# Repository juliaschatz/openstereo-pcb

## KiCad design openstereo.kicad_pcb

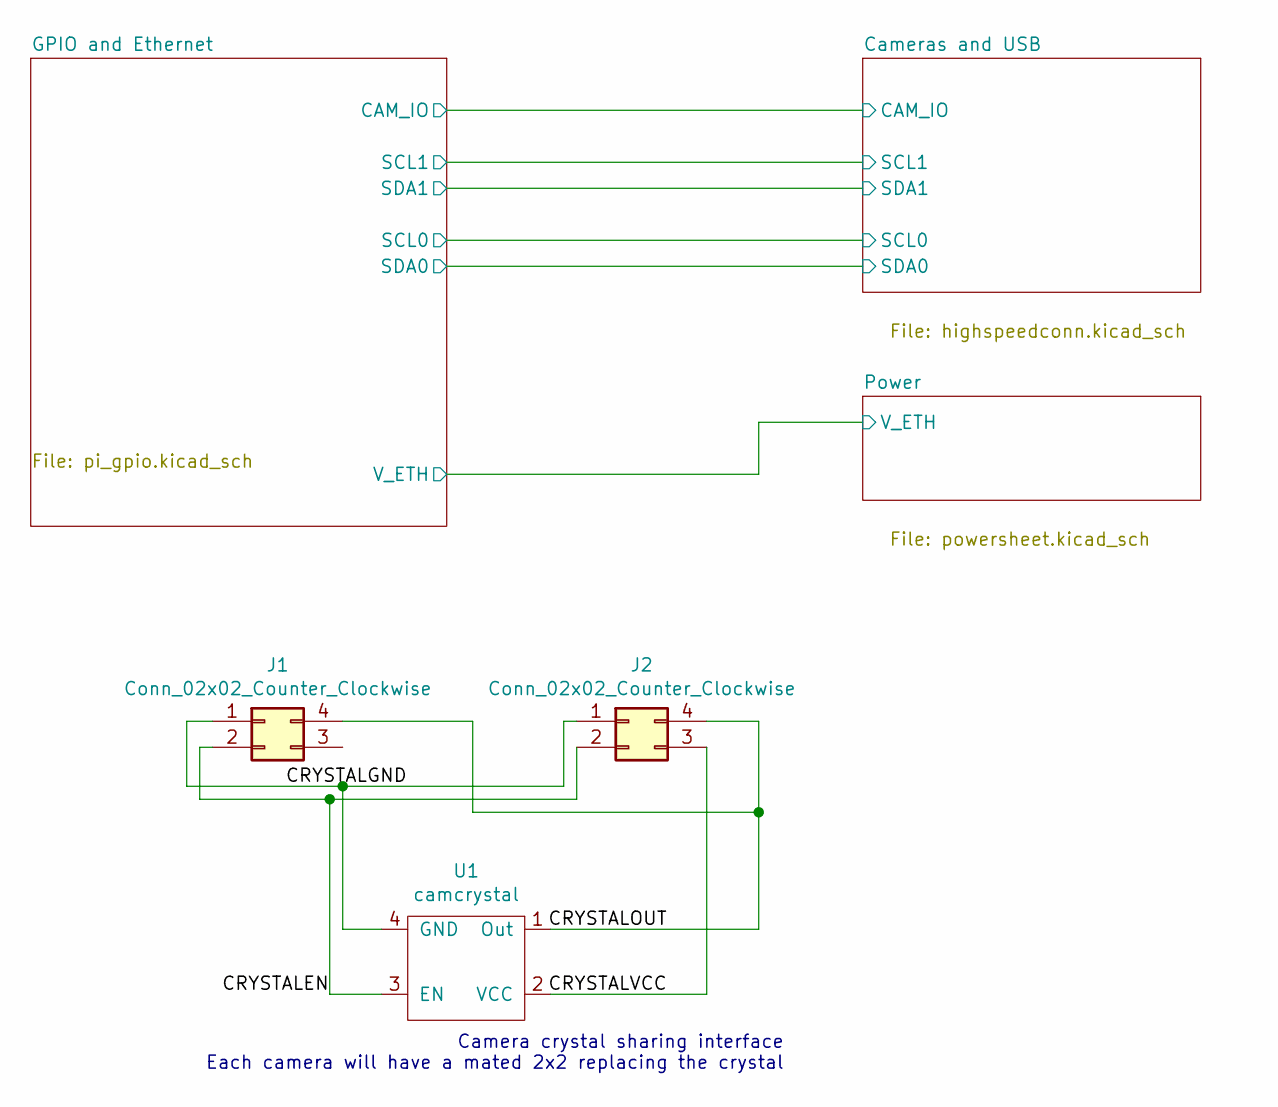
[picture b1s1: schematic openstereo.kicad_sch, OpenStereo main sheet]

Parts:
J1, J2: Conn_02x02_Counter_Clockwise; PinHeader_2x02_P1.27mm_Vertical
U1: camcrystal; crystalpad

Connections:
/CRYSTALEN: J1.2, J2.2, U1.3 (EN)
/CRYSTALGND: J1.1, J2.1, U1.4 (GND)
/CRYSTALOUT: J1.4, J2.4, U1.1 (Out)
/CRYSTALVCC: J2.3, U1.2 (VCC)

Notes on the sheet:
Camera crystal sharing interface Each camera will have a mated 2x2 replacing the crystal

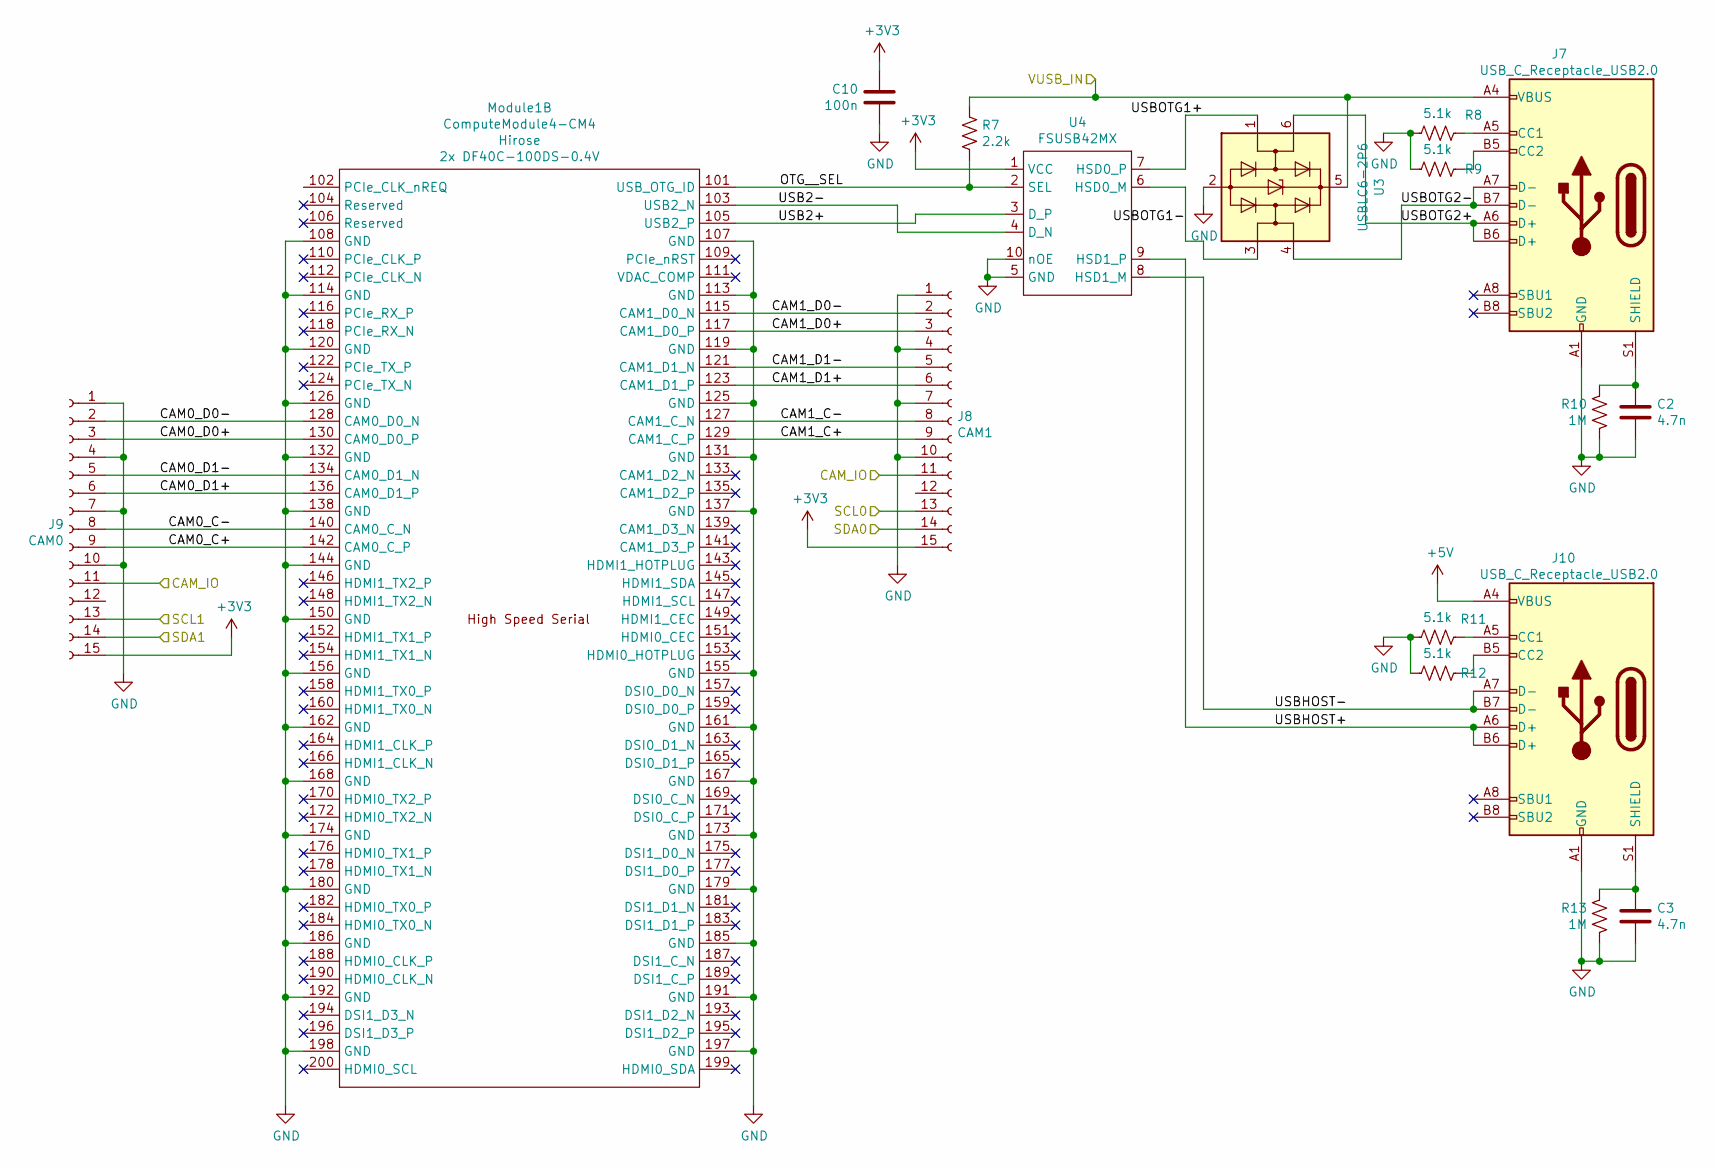
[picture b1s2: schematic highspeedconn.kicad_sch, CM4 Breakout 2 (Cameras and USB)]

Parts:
C2, C3: 4.7n; C_0603_1608Metric
C10: 100n; C_0603_1608Metric
J7, J10: USB_C_Receptacle_USB2.0; USB_C_Receptacle_HRO_TYPE-C-31-M-12
J8: CAM1; SFW15R-2STE1LF
J9: CAM0; SFW15R-2STE1LF
Module1: ComputeModule4-CM4; Raspberry-Pi-4-Compute-Module
R7: 2.2k; R_0603_1608Metric
R8, R9, R11, R12: 5.1k; R_0603_1608Metric
R10, R13: 1M; R_0603_1608Metric
U3: USBLC6-2P6; SOT-666
U4: FSUSB42MX; 10-MSOP-FSUSB

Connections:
+3V3: C10.2, J8.15, J9.15, U4.1 (VCC); also elsewhere on the board
+5V: J10.A4 (VBUS), J10.A9 (VBUS), J10.B4 (VBUS), J10.B9 (VBUS); also elsewhere on the board
/CAM_IO: J8.11, J9.11; also elsewhere on the board
/Cameras and USB/CAM0_C+: J9.9, Module1.142 (CAM0_C_P)
/Cameras and USB/CAM0_C-: J9.8, Module1.140 (CAM0_C_N)
/Cameras and USB/CAM0_D0+: J9.3, Module1.130 (CAM0_D0_P)
/Cameras and USB/CAM0_D0-: J9.2, Module1.128 (CAM0_D0_N)
/Cameras and USB/CAM0_D1+: J9.6, Module1.136 (CAM0_D1_P)
/Cameras and USB/CAM0_D1-: J9.5, Module1.134 (CAM0_D1_N)
/Cameras and USB/CAM1_C+: J8.9, Module1.129 (CAM1_C_P)
/Cameras and USB/CAM1_C-: J8.8, Module1.127 (CAM1_C_N)
/Cameras and USB/CAM1_D0+: J8.3, Module1.117 (CAM1_D0_P)
/Cameras and USB/CAM1_D0-: J8.2, Module1.115 (CAM1_D0_N)
/Cameras and USB/CAM1_D1+: J8.6, Module1.123 (CAM1_D1_P)
/Cameras and USB/CAM1_D1-: J8.5, Module1.121 (CAM1_D1_N)
/Cameras and USB/OTG__SEL: Module1.101 (USB_OTG_ID), R7.2, U4.2 (SEL)
/Cameras and USB/USB2+: Module1.105 (USB2_P), U4.3 (D_P)
/Cameras and USB/USB2-: Module1.103 (USB2_N), U4.4 (D_N)
/Cameras and USB/USBHOST+: J10.A6 (D+), J10.B6 (D+), U4.9 (HSD1_P)
/Cameras and USB/USBHOST-: J10.A7 (D-), J10.B7 (D-), U4.8 (HSD1_M)
/Cameras and USB/USBOTG1+: U3.1 (I/O1), U4.7 (HSD0_P)
/Cameras and USB/USBOTG1-: U3.3 (I/O2), U4.6 (HSD0_M)
/Cameras and USB/USBOTG2+: J7.A6 (D+), J7.B6 (D+), U3.6 (I/O1)
/Cameras and USB/USBOTG2-: J7.A7 (D-), J7.B7 (D-), U3.4 (I/O2)
/Cameras and USB/VUSB_IN: J7.A4 (VBUS), J7.A9 (VBUS), J7.B4 (VBUS), J7.B9 (VBUS), R7.1, U3.5 (VBUS)
/SCL0: J8.13; also elsewhere on the board
/SCL1: J9.13; also elsewhere on the board
/SDA0: J8.14; also elsewhere on the board
/SDA1: J9.14; also elsewhere on the board
GND: C2.1, C3.1, C10.1, J7.A1 (GND), J7.A12 (GND), J7.B1 (GND), J7.B12 (GND), J8.1, J8.4, J8.7, J8.10, J9.1, J9.4, J9.7, J9.10, J10.A1 (GND), J10.A12 (GND), J10.B1 (GND), J10.B12 (GND), Module1.107 (GND), Module1.108 (GND), Module1.113 (GND), Module1.114 (GND), Module1.119 (GND), Module1.120 (GND), Module1.125 (GND), Module1.126 (GND), Module1.131 (GND), Module1.132 (GND), Module1.137 (GND), Module1.138 (GND), Module1.144 (GND), Module1.150 (GND), Module1.155 (GND), Module1.156 (GND), Module1.161 (GND), Module1.162 (GND), Module1.167 (GND), Module1.168 (GND), Module1.173 (GND), Module1.174 (GND), Module1.179 (GND), Module1.180 (GND), Module1.185 (GND), Module1.186 (GND), Module1.191 (GND), Module1.192 (GND), Module1.197 (GND), Module1.198 (GND), R8.1, R9.1, R10.1, R11.1, R12.1, R13.1, U3.2 (GND), U4.5 (GND), U4.10 (nOE); also elsewhere on the board
unnamed: C2.2, J7.S1 (SHIELD), R10.2
unnamed: C3.2, J10.S1 (SHIELD), R13.2
unnamed: J7.A5 (CC1), R8.2
unnamed: J7.B5 (CC2), R9.2
unnamed: J10.A5 (CC1), R11.2
unnamed: J10.B5 (CC2), R12.2
no_connect_106: J10.A8 (SBU1)
no_connect_107: J10.B8 (SBU2)
no_connect_110: J7.A8 (SBU1)
no_connect_111: J7.B8 (SBU2)
no_connect_113: Module1.104 (Reserved)
no_connect_114: Module1.106 (Reserved)
no_connect_115: Module1.109 (PCIe_nRST)
no_connect_116: Module1.110 (PCIe_CLK_P)
no_connect_117: Module1.111 (VDAC_COMP)
no_connect_118: Module1.112 (PCIe_CLK_N)
no_connect_119: Module1.116 (PCIe_RX_P)
no_connect_120: Module1.118 (PCIe_RX_N)
no_connect_121: Module1.122 (PCIe_TX_P)
no_connect_122: Module1.124 (PCIe_TX_N)
no_connect_123: Module1.133 (CAM1_D2_N)
no_connect_124: Module1.135 (CAM1_D2_P)
no_connect_125: Module1.139 (CAM1_D3_N)
no_connect_126: Module1.141 (CAM1_D3_P)
no_connect_127: Module1.143 (HDMI1_HOTPLUG)
no_connect_128: Module1.145 (HDMI1_SDA)
no_connect_129: Module1.146 (HDMI1_TX2_P)
no_connect_130: Module1.147 (HDMI1_SCL)
no_connect_131: Module1.148 (HDMI1_TX2_N)
no_connect_132: Module1.149 (HDMI1_CEC)
no_connect_133: Module1.151 (HDMI0_CEC)
no_connect_134: Module1.152 (HDMI1_TX1_P)
no_connect_135: Module1.153 (HDMI0_HOTPLUG)
no_connect_136: Module1.154 (HDMI1_TX1_N)
no_connect_137: Module1.157 (DSI0_D0_N)
no_connect_138: Module1.158 (HDMI1_TX0_P)
no_connect_139: Module1.159 (DSI0_D0_P)
no_connect_141: Module1.160 (HDMI1_TX0_N)
no_connect_142: Module1.163 (DSI0_D1_N)
no_connect_143: Module1.164 (HDMI1_CLK_P)
no_connect_144: Module1.165 (DSI0_D1_P)
no_connect_145: Module1.166 (HDMI1_CLK_N)
no_connect_146: Module1.169 (DSI0_C_N)
no_connect_147: Module1.170 (HDMI0_TX2_P)
no_connect_148: Module1.171 (DSI0_C_P)
no_connect_149: Module1.172 (HDMI0_TX2_N)
no_connect_150: Module1.175 (DSI1_D0_N)
no_connect_151: Module1.176 (HDMI0_TX1_P)
no_connect_152: Module1.177 (DSI1_D0_P)
no_connect_153: Module1.178 (HDMI0_TX1_N)
no_connect_155: Module1.181 (DSI1_D1_N)
no_connect_156: Module1.182 (HDMI0_TX0_P)
no_connect_157: Module1.183 (DSI1_D1_P)
no_connect_158: Module1.184 (HDMI0_TX0_N)
no_connect_159: Module1.187 (DSI1_C_N)
no_connect_160: Module1.188 (HDMI0_CLK_P)
no_connect_161: Module1.189 (DSI1_C_P)
no_connect_163: Module1.190 (HDMI0_CLK_N)
no_connect_164: Module1.193 (DSI1_D2_N)
no_connect_165: Module1.194 (DSI1_D3_N)
no_connect_166: Module1.195 (DSI1_D2_P)
no_connect_167: Module1.196 (DSI1_D3_P)
no_connect_168: Module1.199 (HDMI0_SDA)
no_connect_169: Module1.200 (HDMI0_SCL)

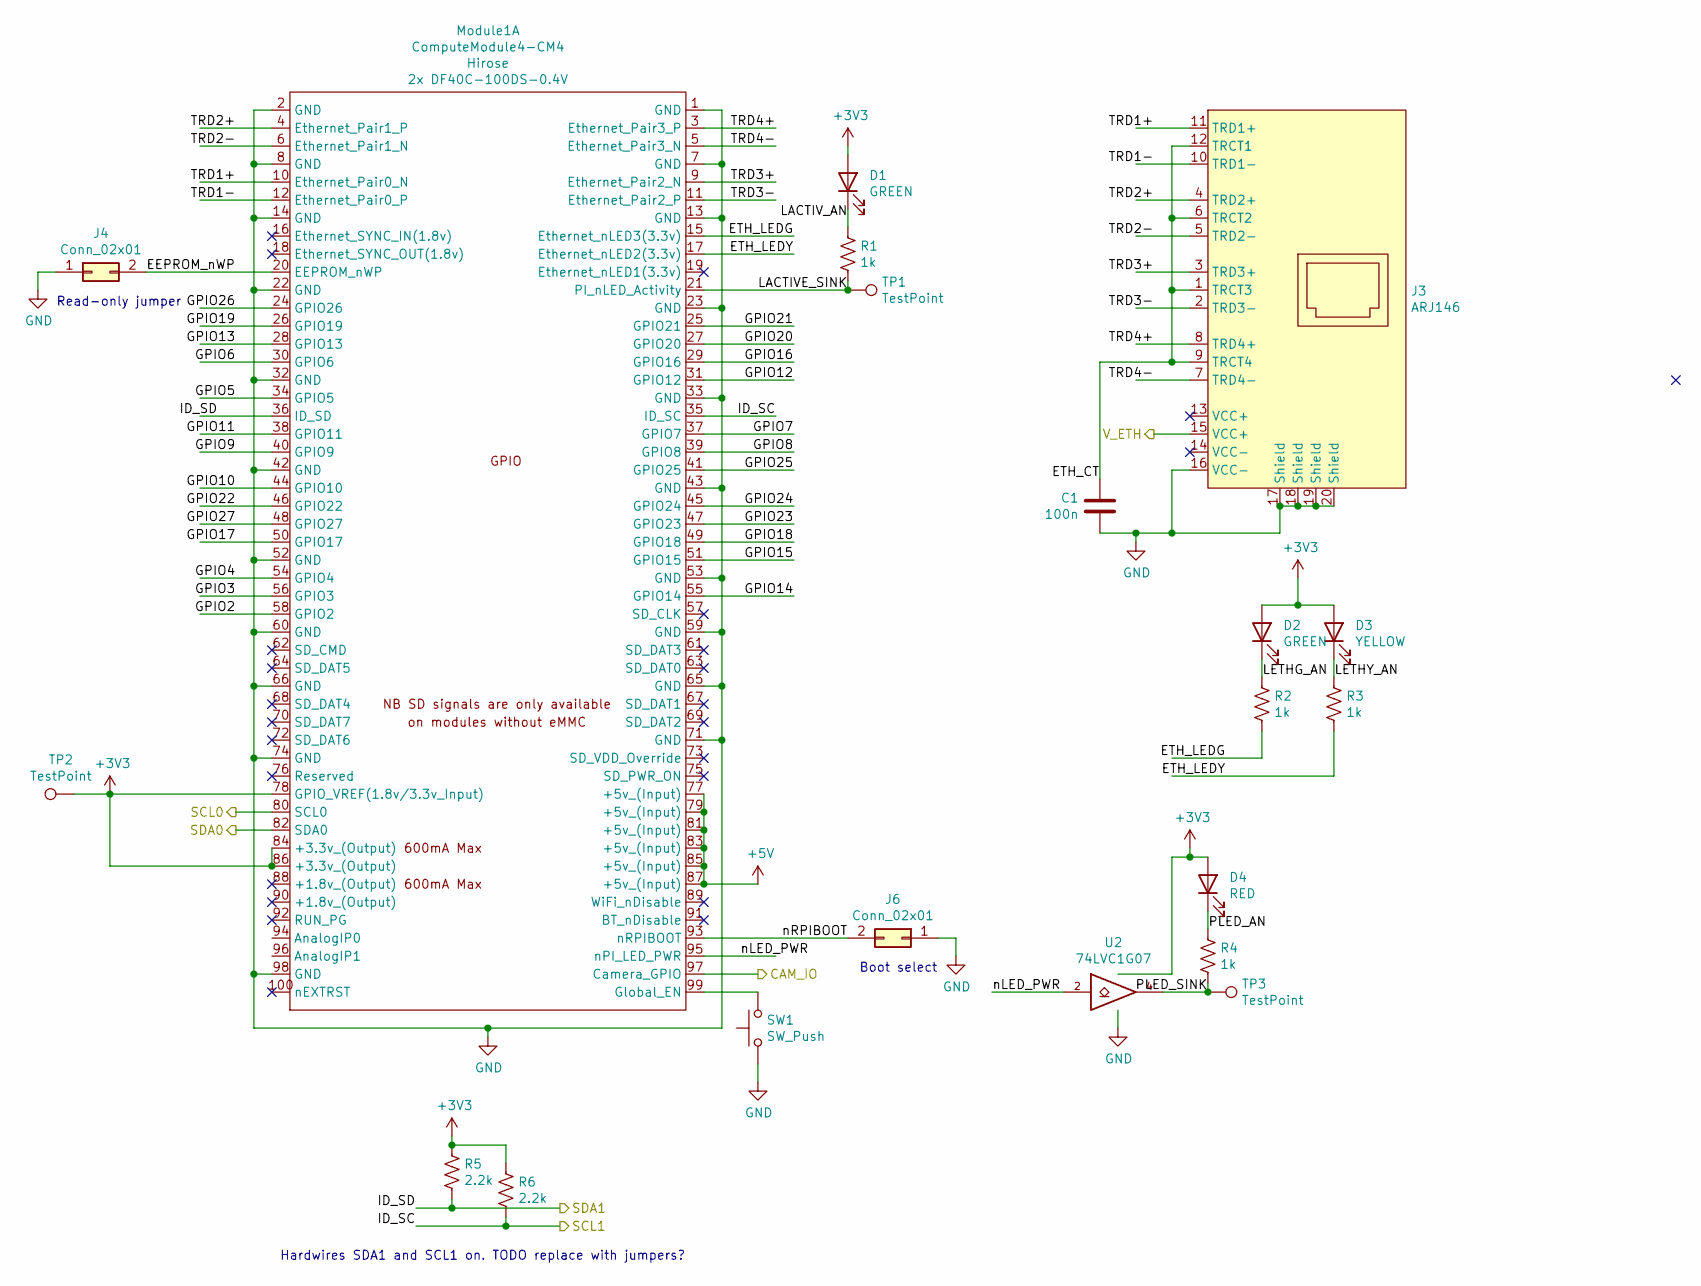
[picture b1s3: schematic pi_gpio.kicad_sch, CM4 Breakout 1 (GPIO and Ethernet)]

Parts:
C1: 100n; C_0603_1608Metric
D1, D2: GREEN; LED_0603_1608Metric
D3: YELLOW; LED_0603_1608Metric
D4: RED; LED_0603_1608Metric
J3: ARJ146
J4, J6: Conn_02x01; PinHeader_2x01_P2.54mm_Vertical
Module1: ComputeModule4-CM4; Raspberry-Pi-4-Compute-Module
R1, R2, R3, R4: 1k; R_0603_1608Metric
R5, R6: 2.2k; R_0603_1608Metric
SW1: SW_Push; SW_Push_1P1T_NO_6x6mm_H9.5mm
TP1, TP2, TP3: TestPoint; TestPoint_Pad_D2.0mm
U2: 74LVC1G07; SOT-23-5

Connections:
+3V3: D1.2 (A), D2.2 (A), D3.2 (A), D4.2 (A), Module1.78 (GPIO_VREF(1.8v/3.3v_Input)), Module1.84 (+3.3v_(Output)), Module1.86 (+3.3v_(Output)), R5.1, R6.1, TP2.1, U2.5 (VCC); also elsewhere on the board
+5V: Module1.77 (+5v_(Input)), Module1.79 (+5v_(Input)), Module1.81 (+5v_(Input)), Module1.83 (+5v_(Input)), Module1.85 (+5v_(Input)), Module1.87 (+5v_(Input)); also elsewhere on the board
/CAM_IO: Module1.97 (Camera_GPIO); also elsewhere on the board
/GPIO and Ethernet/EEPROM_nWP: J4.2, Module1.20 (EEPROM_nWP)
/GPIO and Ethernet/ETH_CT: C1.2, J3.1 (TRCT3), J3.6 (TRCT2), J3.9 (TRCT4), J3.12 (TRCT1)
/GPIO and Ethernet/ETH_LEDG: Module1.15 (Ethernet_nLED3(3.3v)), R2.2
/GPIO and Ethernet/ETH_LEDY: Module1.17 (Ethernet_nLED2(3.3v)), R3.2
/GPIO and Ethernet/GPIO2: Module1.58 (GPIO2)
/GPIO and Ethernet/GPIO3: Module1.56 (GPIO3)
/GPIO and Ethernet/GPIO4: Module1.54 (GPIO4)
/GPIO and Ethernet/GPIO5: Module1.34 (GPIO5)
/GPIO and Ethernet/GPIO6: Module1.30 (GPIO6)
/GPIO and Ethernet/GPIO7: Module1.37 (GPIO7)
/GPIO and Ethernet/GPIO8: Module1.39 (GPIO8)
/GPIO and Ethernet/GPIO9: Module1.40 (GPIO9)
/GPIO and Ethernet/GPIO10: Module1.44 (GPIO10)
/GPIO and Ethernet/GPIO11: Module1.38 (GPIO11)
/GPIO and Ethernet/GPIO12: Module1.31 (GPIO12)
/GPIO and Ethernet/GPIO13: Module1.28 (GPIO13)
/GPIO and Ethernet/GPIO14: Module1.55 (GPIO14)
/GPIO and Ethernet/GPIO15: Module1.51 (GPIO15)
/GPIO and Ethernet/GPIO16: Module1.29 (GPIO16)
/GPIO and Ethernet/GPIO17: Module1.50 (GPIO17)
/GPIO and Ethernet/GPIO18: Module1.49 (GPIO18)
/GPIO and Ethernet/GPIO19: Module1.26 (GPIO19)
/GPIO and Ethernet/GPIO20: Module1.27 (GPIO20)
/GPIO and Ethernet/GPIO21: Module1.25 (GPIO21)
/GPIO and Ethernet/GPIO22: Module1.46 (GPIO22)
/GPIO and Ethernet/GPIO23: Module1.47 (GPIO23)
/GPIO and Ethernet/GPIO24: Module1.45 (GPIO24)
/GPIO and Ethernet/GPIO25: Module1.41 (GPIO25)
/GPIO and Ethernet/GPIO26: Module1.24 (GPIO26)
/GPIO and Ethernet/GPIO27: Module1.48 (GPIO27)
/GPIO and Ethernet/LACTIVE_SINK: Module1.21 (PI_nLED_Activity), R1.2, TP1.1
/GPIO and Ethernet/LACTIV_AN: D1.1 (K), R1.1
/GPIO and Ethernet/LETHG_AN: D2.1 (K), R2.1
/GPIO and Ethernet/LETHY_AN: D3.1 (K), R3.1
/GPIO and Ethernet/PLED_AN: D4.1 (K), R4.1
/GPIO and Ethernet/PLED_SINK: R4.2, TP3.1, U2.4
/GPIO and Ethernet/TRD1+: J3.11 (TRD1+), Module1.10 (Ethernet_Pair0_N)
/GPIO and Ethernet/TRD1-: J3.10 (TRD1-), Module1.12 (Ethernet_Pair0_P)
/GPIO and Ethernet/TRD2+: J3.4 (TRD2+), Module1.4 (Ethernet_Pair1_P)
/GPIO and Ethernet/TRD2-: J3.5 (TRD2-), Module1.6 (Ethernet_Pair1_N)
/GPIO and Ethernet/TRD3+: J3.3 (TRD3+), Module1.9 (Ethernet_Pair2_N)
/GPIO and Ethernet/TRD3-: J3.2 (TRD3-), Module1.11 (Ethernet_Pair2_P)
/GPIO and Ethernet/TRD4+: J3.8 (TRD4+), Module1.3 (Ethernet_Pair3_P)
/GPIO and Ethernet/TRD4-: J3.7 (TRD4-), Module1.5 (Ethernet_Pair3_N)
/GPIO and Ethernet/nLED_PWR: Module1.95 (nPI_LED_PWR), U2.2
/GPIO and Ethernet/nRPIBOOT: J6.2, Module1.93 (nRPIBOOT)
/SCL0: Module1.80 (SCL0); also elsewhere on the board
/SCL1: Module1.35 (ID_SC), R6.2; also elsewhere on the board
/SDA0: Module1.82 (SDA0); also elsewhere on the board
/SDA1: Module1.36 (ID_SD), R5.2; also elsewhere on the board
/V_ETH: J3.15 (VCC+); also elsewhere on the board
GND: C1.1, J3.16 (VCC-), J3.17 (Shield), J3.18 (Shield), J3.19 (Shield), J3.20 (Shield), J4.1, J6.1, Module1.1 (GND), Module1.2 (GND), Module1.7 (GND), Module1.8 (GND), Module1.13 (GND), Module1.14 (GND), Module1.22 (GND), Module1.23 (GND), Module1.32 (GND), Module1.33 (GND), Module1.42 (GND), Module1.43 (GND), Module1.52 (GND), Module1.53 (GND), Module1.59 (GND), Module1.60 (GND), Module1.65 (GND), Module1.66 (GND), Module1.71 (GND), Module1.74 (GND), Module1.98 (GND), SW1.2, U2.3 (GND); also elsewhere on the board
unnamed: Module1.99 (Global_EN), SW1.1
no_connect_108: J3.13 (VCC+)
no_connect_109: J3.14 (VCC-)
no_connect_112: Module1.100 (nEXTRST)
no_connect_140: Module1.16 (Ethernet_SYNC_IN(1.8v))
no_connect_154: Module1.18 (Ethernet_SYNC_OUT(1.8v))
no_connect_162: Module1.19 (Ethernet_nLED1(3.3v))
no_connect_170: Module1.57 (SD_CLK)
no_connect_171: Module1.61 (SD_DAT3)
no_connect_172: Module1.62 (SD_CMD)
no_connect_173: Module1.63 (SD_DAT0)
no_connect_174: Module1.64 (SD_DAT5)
no_connect_175: Module1.67 (SD_DAT1)
no_connect_176: Module1.68 (SD_DAT4)
no_connect_177: Module1.69 (SD_DAT2)
no_connect_178: Module1.70 (SD_DAT7)
no_connect_179: Module1.72 (SD_DAT6)
no_connect_180: Module1.73 (SD_VDD_Override)
no_connect_181: Module1.75 (SD_PWR_ON)
no_connect_182: Module1.76 (Reserved)
no_connect_183: Module1.88 (+1.8v_(Output))
no_connect_184: Module1.89 (WiFi_nDisable)
no_connect_185: Module1.90 (+1.8v_(Output))
no_connect_186: Module1.91 (BT_nDisable)
no_connect_187: Module1.92 (RUN_PG)

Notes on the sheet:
Read-only jumper
Hardwires SDA1 and SCL1 on. TODO replace with jumpers?
Boot select

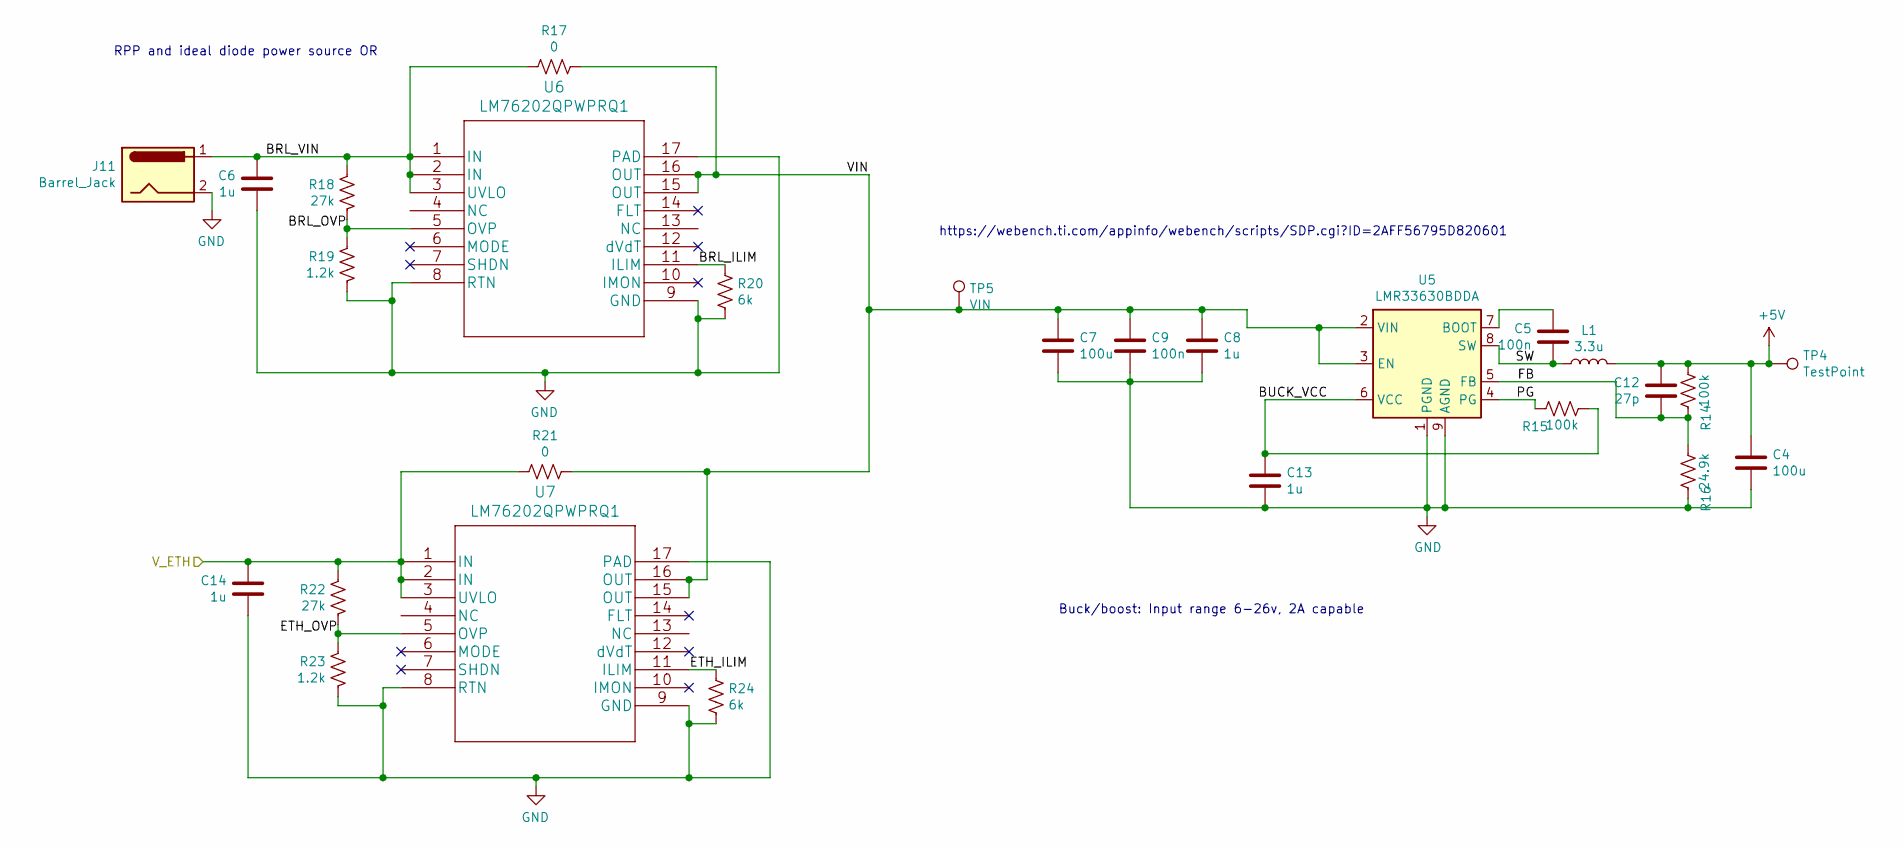
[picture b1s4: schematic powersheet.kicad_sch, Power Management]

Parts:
C4, C7: 100u; CP_Elec_8x10.5
C5, C9: 100n; C_0603_1608Metric
C6, C8, C13, C14: 1u; C_0603_1608Metric
C12: 27p; C_0603_1608Metric
J11: Barrel_Jack; CUI_PJ-037A
L1: 3.3u; L_6.3x6.3_H3
R14, R15: 100k; R_0603_1608Metric
R16: 24.9k; R_0603_1608Metric
R17, R21: 0; R_0603_1608Metric
R18, R22: 27k; R_0603_1608Metric
R19, R23: 1.2k; R_0603_1608Metric
R20, R24: 6k; R_0603_1608Metric
TP4: TestPoint; TestPoint_Pad_D2.0mm
TP5: VIN; TestPoint_Pad_D2.0mm
U5: LMR33630BDDA; Texas_HSOP-8-1EP_3.9x4.9mm_P1.27mm_ThermalVias
U6, U7: LM76202QPWPRQ1

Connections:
+5V: C4.1, C12.2, L1.2, R14.1, TP4.1; also elsewhere on the board
/Power/BRL_ILIM: R20.1, U6.11 (ILIM)
/Power/BRL_OVP: R18.1, R19.2, U6.5 (OVP)
/Power/BRL_VIN: C6.2, J11.1, R17.1, R18.2, U6.1 (IN), U6.2 (IN), U6.3 (UVLO)
/Power/BUCK_VCC: C13.1, R15.1, U5.6 (VCC)
/Power/ETH_ILIM: R24.1, U7.11 (ILIM)
/Power/ETH_OVP: R22.1, R23.2, U7.5 (OVP)
/Power/FB: C12.1, R14.2, R16.1, U5.5 (FB)
/Power/PG: R15.2, U5.4 (PG)
/Power/SW: C5.1, L1.1, U5.8 (SW)
/Power/VIN: C7.1, C8.1, C9.1, R17.2, R21.2, TP5.1, U5.2 (VIN), U5.3 (EN), U6.15 (OUT), U6.16 (OUT), U7.15 (OUT), U7.16 (OUT)
/V_ETH: C14.2, R21.1, R22.2, U7.1 (IN), U7.2 (IN), U7.3 (UVLO); also elsewhere on the board
GND: C4.2, C6.1, C7.2, C8.2, C9.2, C13.2, C14.1, J11.2, R16.2, R19.1, R20.2, R23.1, R24.2, U5.1 (PGND), U5.9 (AGND), U6.8 (RTN), U6.9 (GND), U6.17 (PAD), U7.8 (RTN), U7.9 (GND), U7.17 (PAD); also elsewhere on the board
unnamed: C5.2, U5.7 (BOOT)
no_connect_188: U6.10 (IMON)
no_connect_189: U6.12 (dVdT)
no_connect_190: U6.14 (FLT)
no_connect_191: U6.6 (MODE)
no_connect_192: U6.7 (SHDN)
no_connect_193: U7.10 (IMON)
no_connect_194: U7.12 (dVdT)
no_connect_195: U7.14 (FLT)
no_connect_196: U7.6 (MODE)
no_connect_197: U7.7 (SHDN)

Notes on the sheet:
RPP and ideal diode power source OR
Buck/boost: Input range 6-26v, 2A capable
https://webench.ti.com/appinfo/webench/scripts/SDP.cgi?ID=2AFF56795D820601

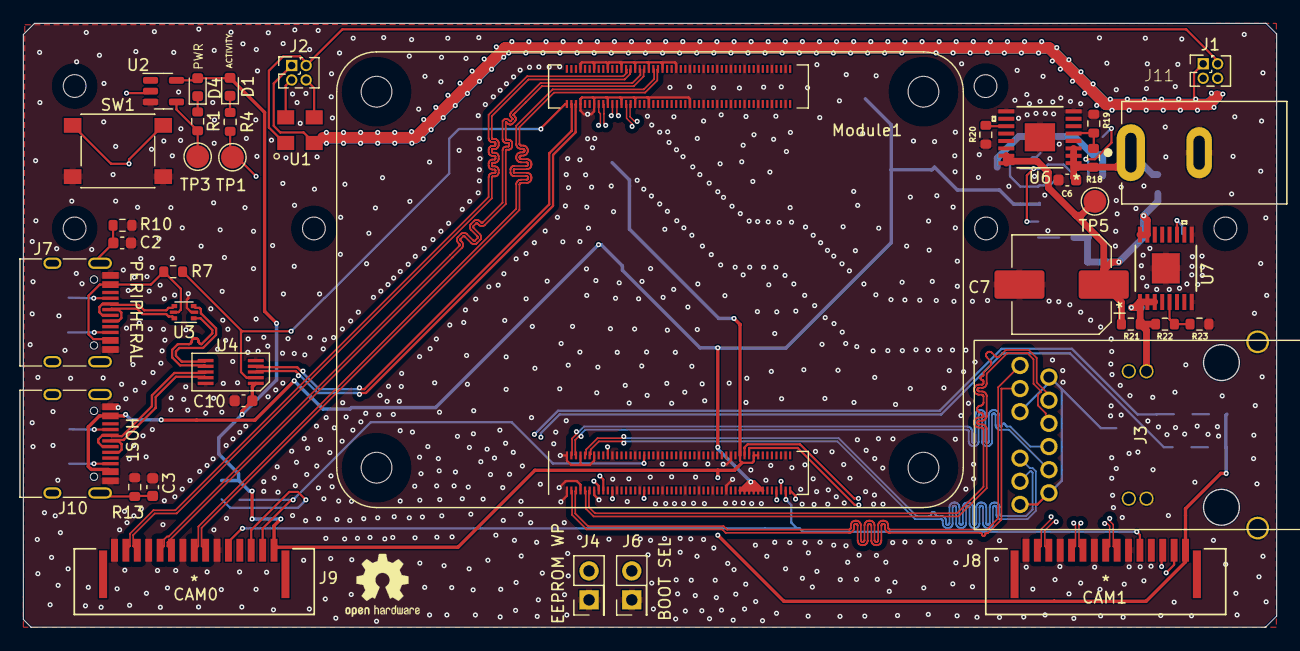
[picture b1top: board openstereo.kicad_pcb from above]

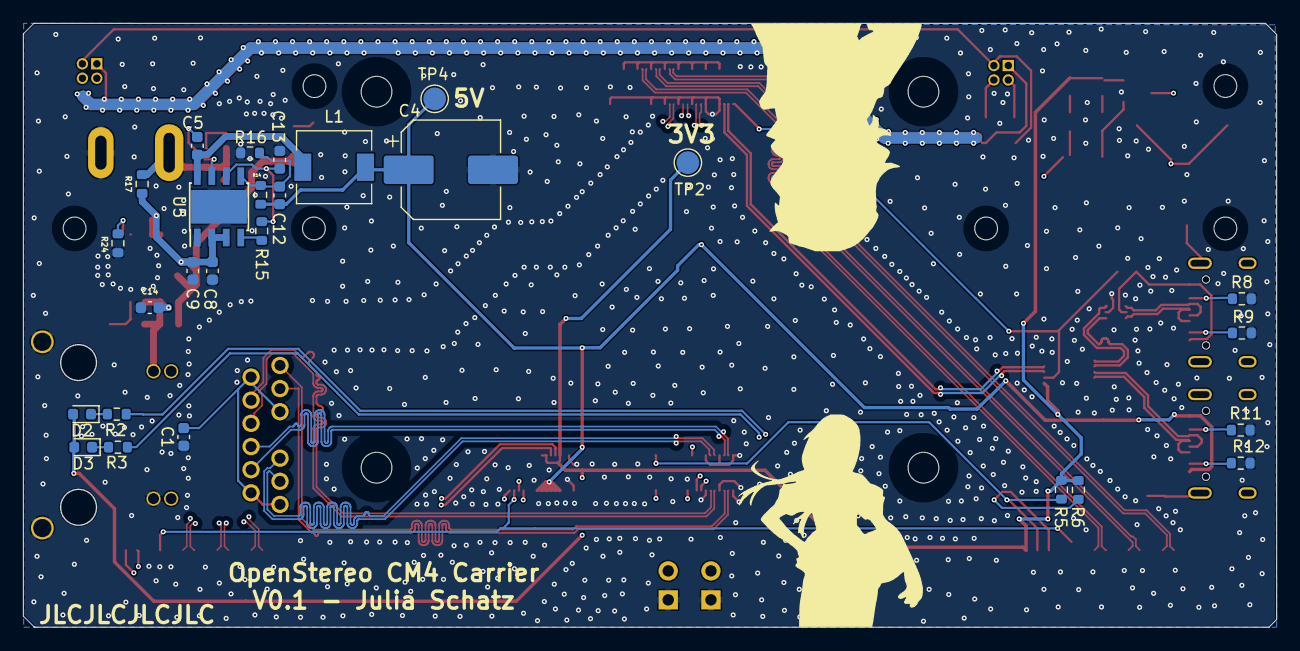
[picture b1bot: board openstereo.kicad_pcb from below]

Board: 4 copper layers, 110.0 x 53.0 mm, 66 parts (27 on the bottom side), 73 nets.

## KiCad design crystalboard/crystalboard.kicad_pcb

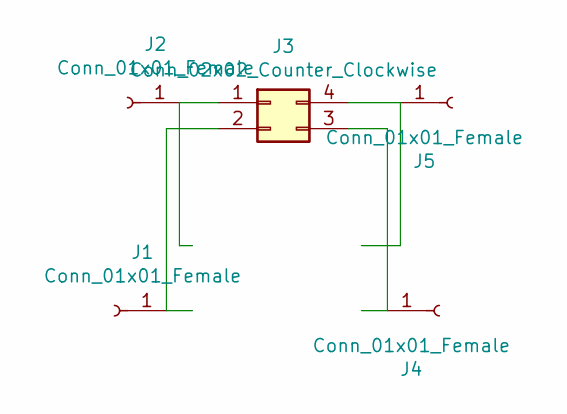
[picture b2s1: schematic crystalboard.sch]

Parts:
J1, J2, J4, J5: Conn_01x01_Female; PinHeader_1x01_P1.00mm_Vertical
J3: Conn_02x02_Counter_Clockwise; PinHeader_2x02_P1.27mm_Vertical_SMD

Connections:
unnamed: J1.1, J3.2
unnamed: J2.1, J3.1
unnamed: J3.3, J4.1
unnamed: J3.4, J5.1

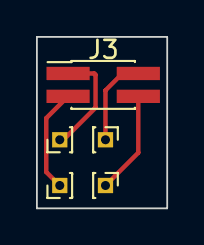
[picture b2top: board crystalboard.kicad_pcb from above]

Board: 2 copper layers, 7.2 x 9.5 mm, 5 parts (0 on the bottom side), 4 nets.

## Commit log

2021-02-01 Initial commit.
    Version 0.1

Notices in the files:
parts and their libraries:
Copyright 2016 Accelerated Designs. All rights reserved.
